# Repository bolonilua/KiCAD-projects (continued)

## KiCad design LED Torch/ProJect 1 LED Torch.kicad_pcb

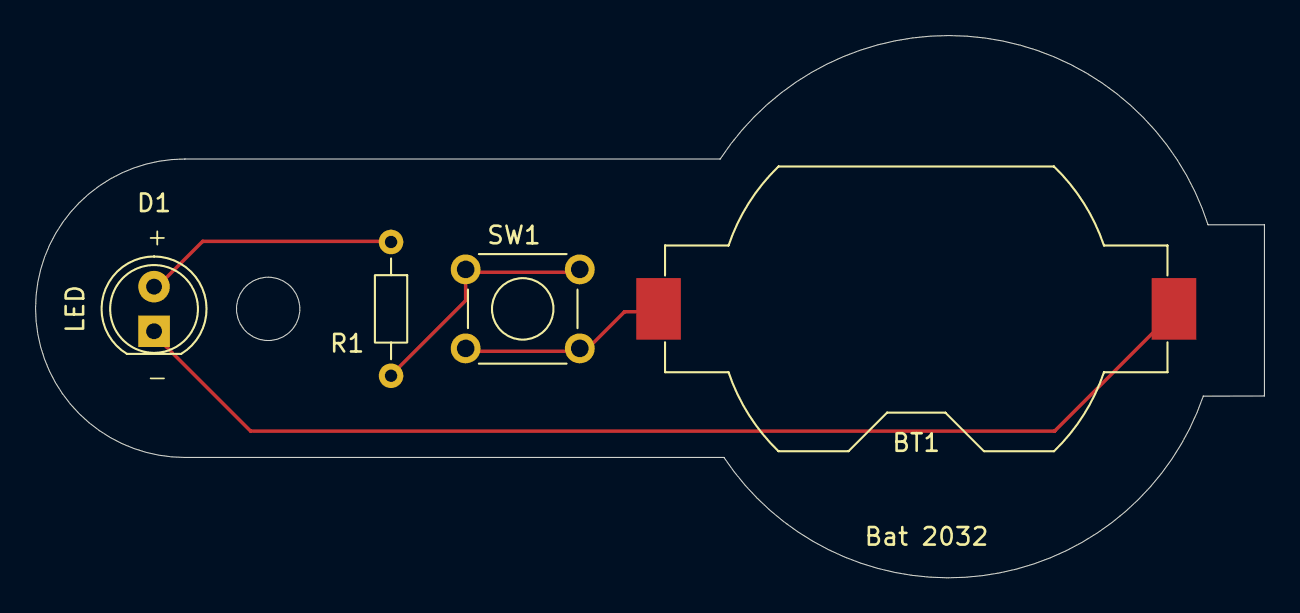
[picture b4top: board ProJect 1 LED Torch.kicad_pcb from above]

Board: 2 copper layers, 70.0 x 30.9 mm, 4 parts (0 on the bottom side), 4 nets.

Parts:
BT1: Bat 2032; BatteryHolder_Keystone_1058_1x2032
D1: LED; LED_D5.0mm
R1: R; R_Axial_DIN0204_L3.6mm_D1.6mm_P7.62mm_Horizontal
SW1: SW_DPDT_x2; SW_TH_Tactile_Omron_B3F-100x

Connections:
/LED_anode: D1.2 (A), R1.1
/LED_cathode: BT1.2 (-), D1.1 (K)
/bat_pos: BT1.1 (+), SW1.2 (B)
/sw_R: R1.2, SW1.1 (A)

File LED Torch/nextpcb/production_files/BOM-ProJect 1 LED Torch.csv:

MPN,Qty,Designator,value,manufacturer,Category,SKU,Customer Supply,Customer Remark
,1,BT1,Bat 2032,,,
,1,D1,LED,,,
,1,R1,R,,,
,1,SW1,SW_DPDT_x2,,,

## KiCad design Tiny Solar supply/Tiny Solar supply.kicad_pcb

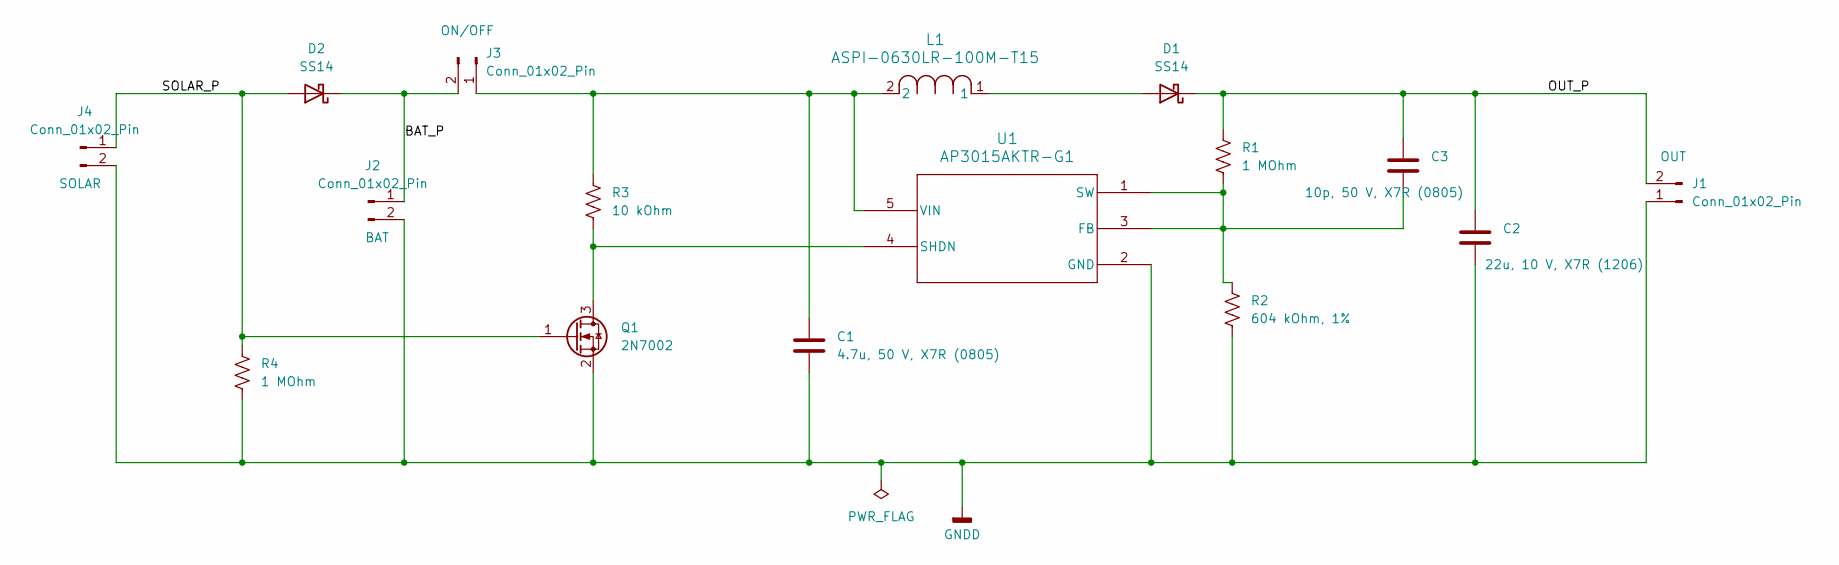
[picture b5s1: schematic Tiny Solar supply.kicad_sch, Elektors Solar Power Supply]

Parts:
C1: 4.7u, 50 V, X7R (0805); C_0805_2012Metric
C2: 22u, 10 V, X7R (1206); C_1206_3216Metric
C3: 10p, 50 V, X7R (0805); C_0805_2012Metric
D1, D2: SS14; D_SMA
J1, J2, J3: Conn_01x02_Pin; PinHeader_1x02_P2.54mm_Vertical
J4: Conn_01x02_Pin; PinHeader_1x02_P2.54mm_Horizontal
L1: ASPI-0630LR-100M-T15; IND_ASPI-0630LR_ABR
Q1: 2N7002; SOT-23
R1, R4: 1 MOhm; R_0805_2012Metric
R2: 604 kOhm, 1%; R_0805_2012Metric
R3: 10 kOhm; R_0805_2012Metric
U1: AP3015AKTR-G1; SOT23-5_1P55X2P9_DIO

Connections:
/BAT_P: D2.1 (K), J2.1, J3.2
/OUT_P: C2.1, C3.1, D1.1 (K), J1.2, R1.1
/SOLAR_P: D2.2 (A), J4.1, Q1.1 (G), R4.1
GNDD: C1.2, C2.2, J1.1, J2.2, J4.2, Q1.2 (S), R2.2, R4.2, U1.2 (GND)
unnamed: D1.2 (A), L1.1
unnamed: C1.1, J3.1, L1.2, R3.1, U1.5 (VIN)
unnamed: Q1.3 (D), R3.2, U1.4 (SHDN)
unnamed: C3.2, R1.2, R2.1, U1.1 (SW), U1.3 (FB)

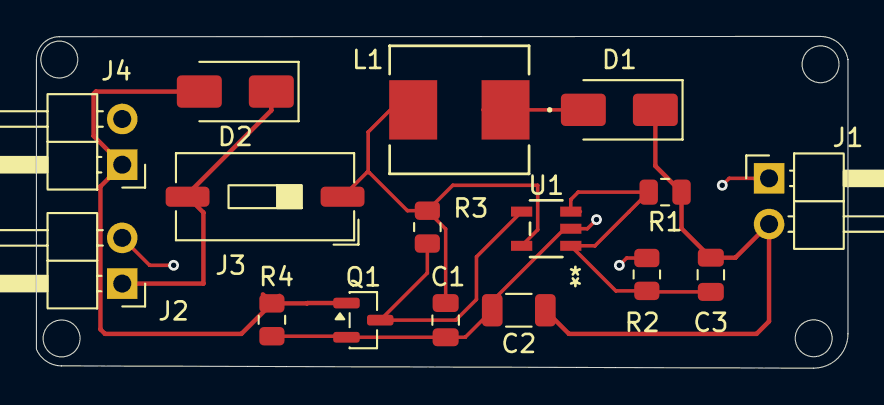
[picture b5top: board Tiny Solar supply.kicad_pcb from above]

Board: 2 copper layers, 45.1 x 18.4 mm, 16 parts (0 on the bottom side), 8 nets.

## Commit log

2026-03-08 main: First PCB git repo implementation
2026-03-08 experimental: just a test
2026-03-08 main: setup of EE schema for new project
2026-03-10 main: Added symbols to schematic sheets
2026-03-10 main: Annotated symbol in schematic as needed
2026-03-10 main: Added component values
2026-03-10 main: Assigned footprints to all parts
2026-03-10 main: Wired sheet 1 with connections and nets
2026-03-12 New computer update with complete schematic connections
2026-03-12 main: Finalizing schematic
2026-03-20 2layer: setting up pcb
2026-03-20 2layer: Completed placement of footprint
2026-03-24 2layer: routing completed
2026-03-24 2layer: refined routing
2026-03-27 2layer: routing and silkscreen complete
2026-03-27 2layer: Completed 2 layer pcb project and added gerber for manufacturing
2026-03-28 2layer: Completed 20-layerPCB.
2026-03-28 main: improved git ignore
2026-03-28 4layer: Completed 4layer routing of MCUdatalogger
2026-03-30 4layer: completed 4 layer routing
2026-03-30 main: edit git attribute file to ignore pcb files during merge
2026-03-30 main: updated schematic due to SCL and SCK mixup
2026-03-30 2layer: updating git ignore
2026-03-30 main: cleanup
2026-03-30 main: more cleanup
2026-03-30 2layer: merged with fix from main and now adding attributes
2026-03-30 4layer: adding attributes
2026-03-30 4layer: recovered and corrected 4layer
2026-03-30 main: adding attributes
2026-04-01 main: updating main
2026-04-07 main: cleaning up
2026-04-09 main: first effort at ESP32
2026-04-09 main: update to project
2026-04-11 main: closed out schematics
2026-04-20 main: updating layout
2026-04-20 main: updating layout with lock
2026-04-26 main: updated placement
2026-04-28 main: added copper zones
